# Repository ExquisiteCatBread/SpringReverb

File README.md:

# SpringReverb
Guitar effect based on reverb tank

See "Spring reverb project documentation.pdf"

.jpg)

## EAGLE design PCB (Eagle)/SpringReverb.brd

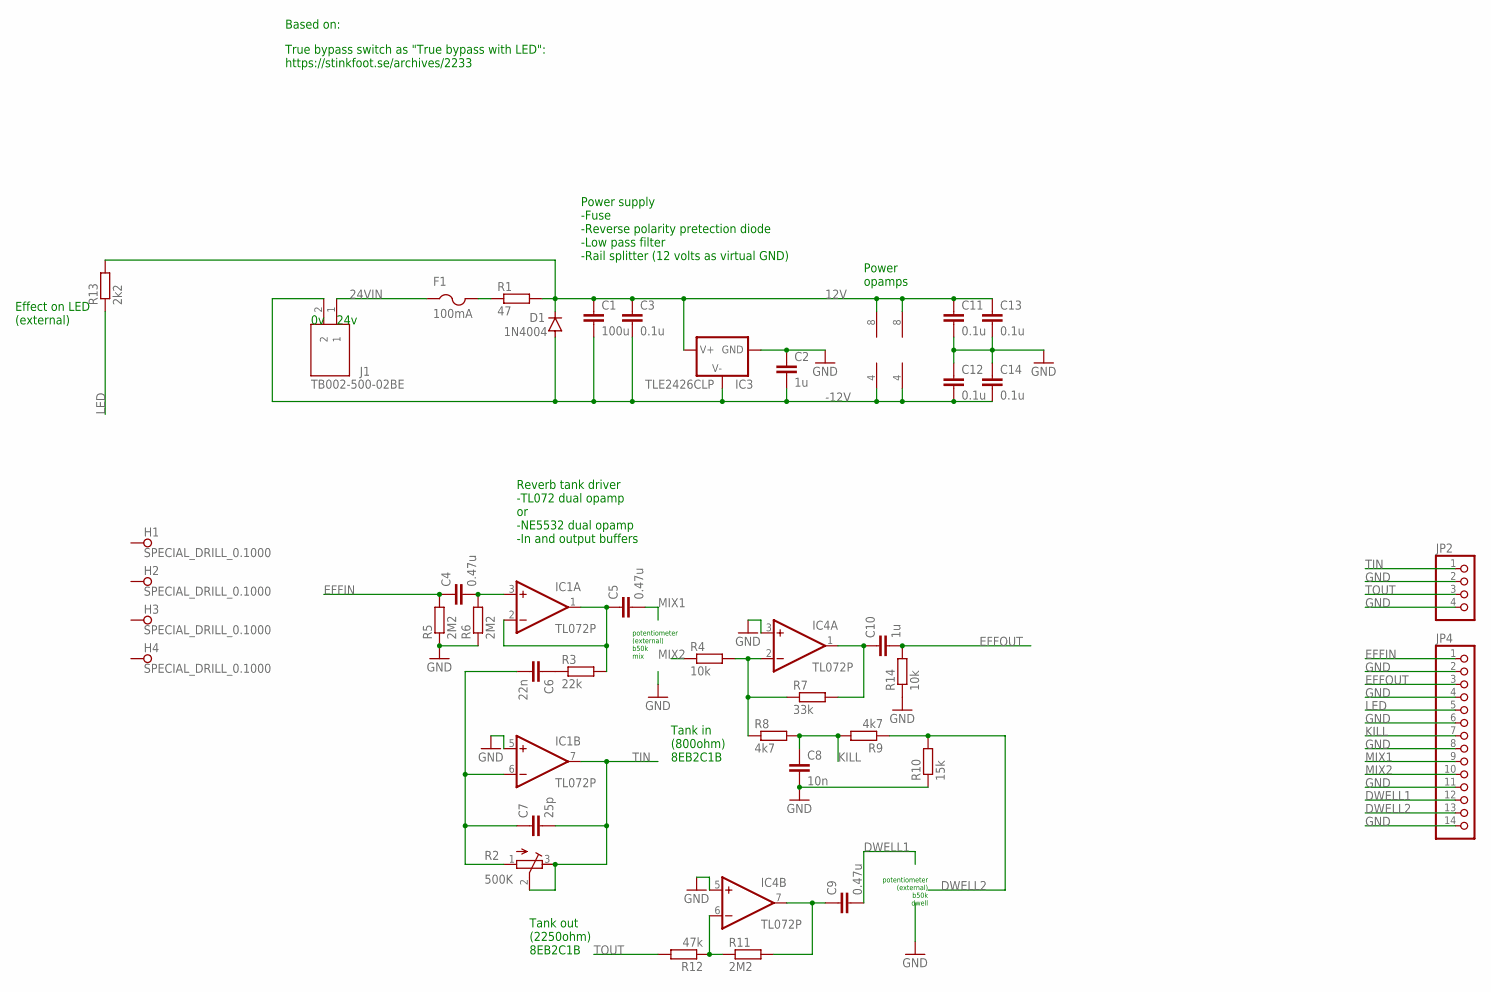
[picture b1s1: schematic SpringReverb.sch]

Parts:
C1: 100u; C1206
C2, C10: 1u; C1206
C3, C11, C12, C13, C14: 0.1u; C0603
C4, C5, C9: 0.47u; C1206
C6: 22n; C0603
C7: 25p; C1206
C8: 10n; C1206
D1: 1N4004; DO41-10
F1: 100mA; 1812
H1, H2, H3, H4: SPECIAL_DRILL_0.1000; PAD_0.1000
IC1, IC4: TL072P; DIL08
IC3: TLE2426CLP; TO92LP
J1: TB002-500-02BE; CUI_TB002-500-02BE
JP2: PINHD-1X4; 1X04
JP4: PINHD-1X14; 1X14
R1: 47; R0603
R2: 500K; RTRIM3296W
R3: 22k; R0603
R4, R14: 10k; R0603
R5, R6, R11: 2M2; R1206
R7: 33k; R0603
R8, R9: 4k7; R0603
R10: 15k; R1206
R12: 47k; R0603
R13: 2k2; R0603

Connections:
12V: C1.1, C3.1, C11.1, C13.1, D1.C, IC1.8 (V+), IC3.IN, IC4.8 (V+), R1.2, R13.2
24VIN: F1.1, J1.1
-12V: C1.2, C2.2, C3.2, C12.2, C14.2, D1.A, IC1.4 (V-), IC3.GND, IC4.4 (V-), J1.2
DWELL1: C9.2, JP4.12
DWELL2: JP4.13, R9.1, R10.2
EFFIN: C4.1, JP4.1, R5.2
EFFOUT: C10.2, JP4.3, R14.2
GND: C2.1, C8.2, C11.2, C12.1, C13.2, C14.1, IC1.5 (+IN), IC3.OUT, IC4.3 (+IN), IC4.5 (+IN), JP2.2, JP2.4, JP4.2, JP4.4, JP4.6, JP4.8, JP4.11, JP4.14, R5.1, R6.1, R10.1, R14.1
KILL: C8.1, JP4.7, R8.2, R9.2
LED: JP4.5, R13.1
MIX1: C5.2, JP4.9
MIX2: JP4.10, R4.1
unnamed: C4.2, IC1.3 (+IN), R6.2
unnamed: F1.2, R1.1
unnamed: C5.1, IC1.1 (OUT), IC1.2 (-IN), R3.2
unnamed: C6.1, R3.1
unnamed: C6.2, C7.1, IC1.6 (-IN), R2.1 (A)
unnamed: IC4.2 (-IN), R4.2, R7.1, R8.1
unnamed: C10.1, IC4.1 (OUT), R7.2
unnamed: C9.1, IC4.7 (OUT), R11.2
unnamed: IC4.6 (-IN), R11.1, R12.1
TIN: C7.2, IC1.7 (OUT), JP2.1, R2.2 (S), R2.3 (E)
TOUT: JP2.3, R12.2

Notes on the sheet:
Power supply -Fuse -Reverse polarity pretection diode -Low pass filter -Rail splitter (12 volts as virtual GND)
potentiometer (external) b50k mix
Reverb tank driver -TL072 dual opamp or -NE5532 dual opamp -In and output buffers
Based on:
potentiometer (external) b50k dwell
Effect on LED (external)
True bypass switch as "True bypass with LED": https://stinkfoot.se/archives/2233
24v
Power opamps
Tank in (800ohm) 8EB2C1B
Tank out (2250ohm) 8EB2C1B

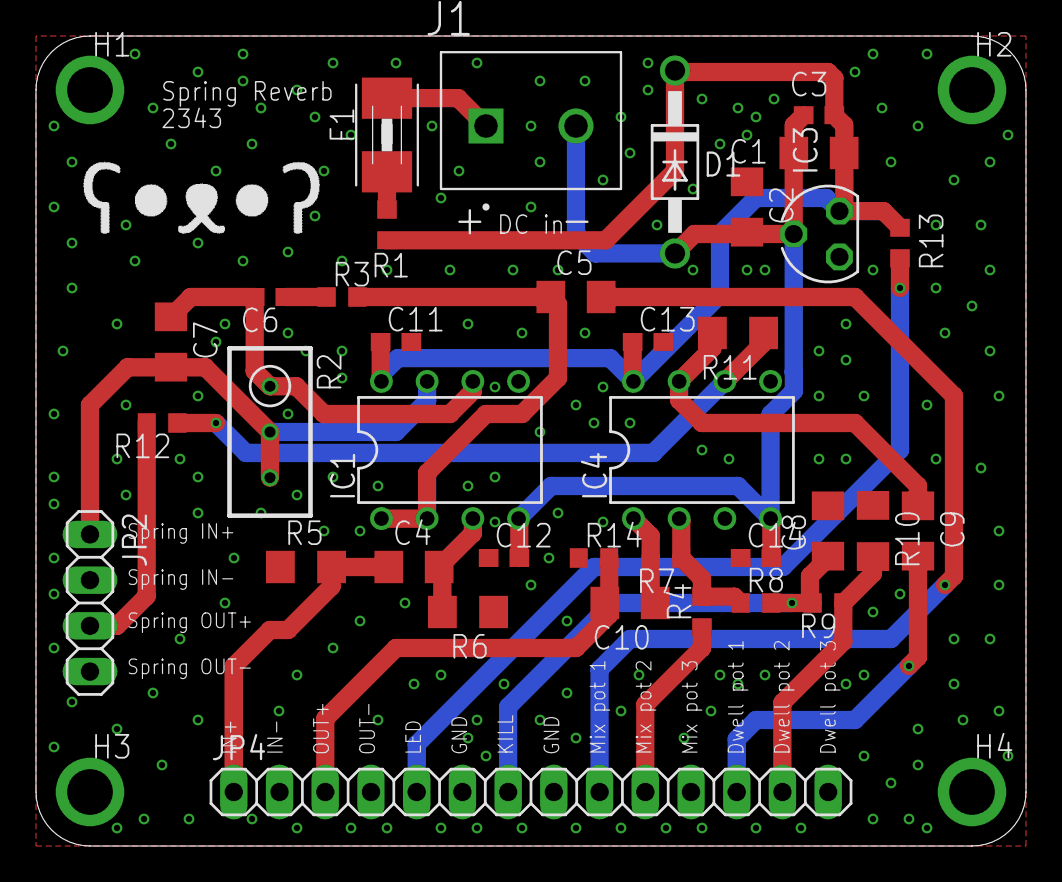
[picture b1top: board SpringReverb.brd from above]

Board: 2 copper layers, 55.0 x 45.0 mm, 40 parts (0 on the bottom side), 23 nets.

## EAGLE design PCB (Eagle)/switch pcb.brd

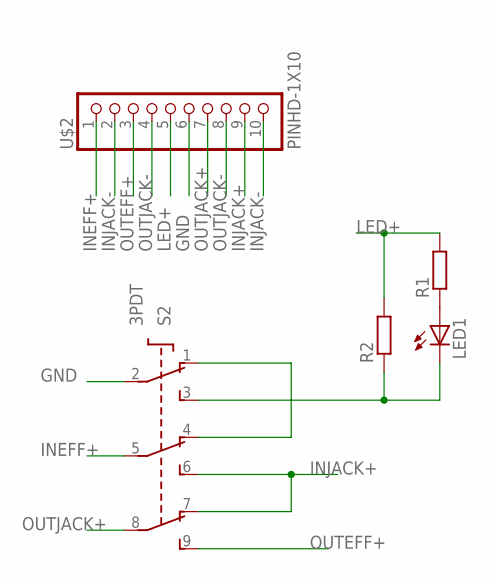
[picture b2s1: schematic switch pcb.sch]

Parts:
LED1: LED3MM
R1, R2: R-EU_R0603; R0603
S2: 3PDT
U$2: PINHD-1X10; 1X10-BIG

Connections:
GND: S2.2 (P1), U$2.6
INEFF+: S2.5 (P2), U$2.1
INJACK+: S2.6 (S2), S2.7 (O3), U$2.9
INJACK-: U$2.2, U$2.10
LED+: R1.2, R2.2, U$2.5
unnamed: LED1.A, R1.1
unnamed: LED1.K (C), R2.1, S2.3 (S1)
unnamed: S2.1 (O1), S2.4 (O2)
OUTEFF+: S2.9 (S3), U$2.3
OUTJACK+: S2.8 (P3), U$2.7
OUTJACK-: U$2.4, U$2.8

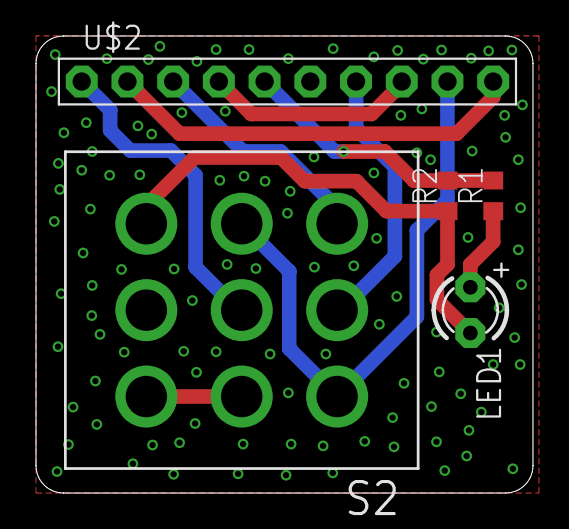
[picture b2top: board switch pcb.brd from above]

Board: 2 copper layers, 27.6 x 25.4 mm, 5 parts (0 on the bottom side), 11 nets.

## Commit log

2023-10-22 First
    first version of spring reverb driver pcb and 3pdt switch
2023-11-04 Update first release PCB
2023-11-04 Update with doc
2023-11-04 update pic
2023-11-04 names
2023-11-05 Update switchPCB to version 4423
    Corrected footprint for 3PDT switch.
    Updated documentation.
2023-11-08 Replaced C6
    Replaced C6 (0.1uF) with 22nF for less bass on tank input, therefore less muddy sound
2023-11-11 Update Spring reverb project documentation.pdf
    Added BOM and cost calculation
2023-11-24 3pdt switch mounting
    Mounted 3pdt switch a bit better. with a 3d printed spacer ring. Replaced switch PCB with new version in photos.
